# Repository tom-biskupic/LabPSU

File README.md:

# LabPSU
Open Source Lab Power Supply

This project is to create an open source modular lab power supply. The power supply is designed to:

* Provide between 0-15V @ 5A and 15-30V @ 3A
* Provide current limiting
* Voltage to be settable to within 1mV and current limit to 1mA resolution.
* Voltage/current readback to 1mV and 1mA with low temperature drift.
* Limit heat loss through the use of a pre-regulator. The pre-regulator uses an SCR and MOSFET arrangement to reduce noise (switches at a low frequency)
* Digitally controllable via a Raspberry PI and touch-screen interface.
* Multiple channels (designed for 3).
* Each channel is isolated and can be paralleled or put in series.
* Each channel uses its own torroidal transformer.

A Blog documenting the development of the project can be found here http://wahz.blogspot.com.au/2015/03/lab-power-supply-project.html

The major components used in the project are:

* IRFP044N N-channel MOSFET as the pass device. http://www.irf.com/product-info/datasheets/data/irfp044n.pdf
* IRF5210 P-channel MOSFET used to switch the input in the pre-regulator http://www.irf.com/product-info/datasheets/data/irf5210.pdf
* MCR-100 SCR http://www.onsemi.com/pub_link/Collateral/MCR100-D.PDF
* LT1639 Op Amps used in the control loop. http://www.linear.com/product/LT1639
* LT1716 Comparator used in the pre-regulator http://cds.linear.com/docs/en/datasheet/1716fa.pdf
* LTC2050 Op Amp used for current sense amplifier. http://www.linear.com/product/LTC2050
* AD5689R DAC with built in 2ppm/degree reference as main output voltage/current DAC. http://www.analog.com/media/en/technical-documentation/data-sheets/AD5689_5687.pdf
* AD7705 ADC used to read output voltage/current http://www.analog.com/media/en/technical-documentation/data-sheets/AD7705_7706.pdf
* ATMEGA328P Used as the main controller
* ADUM1201 dual channel isolator used to isolate the USB interface from the rest of the module http://www.analog.com/media/en/technical-documentation/data-sheets/ADuM1200_1201.pdf
* MCP2200 USB to serial converter http://www.microchip.com/wwwproducts/devices.aspx?dDocName=en546923

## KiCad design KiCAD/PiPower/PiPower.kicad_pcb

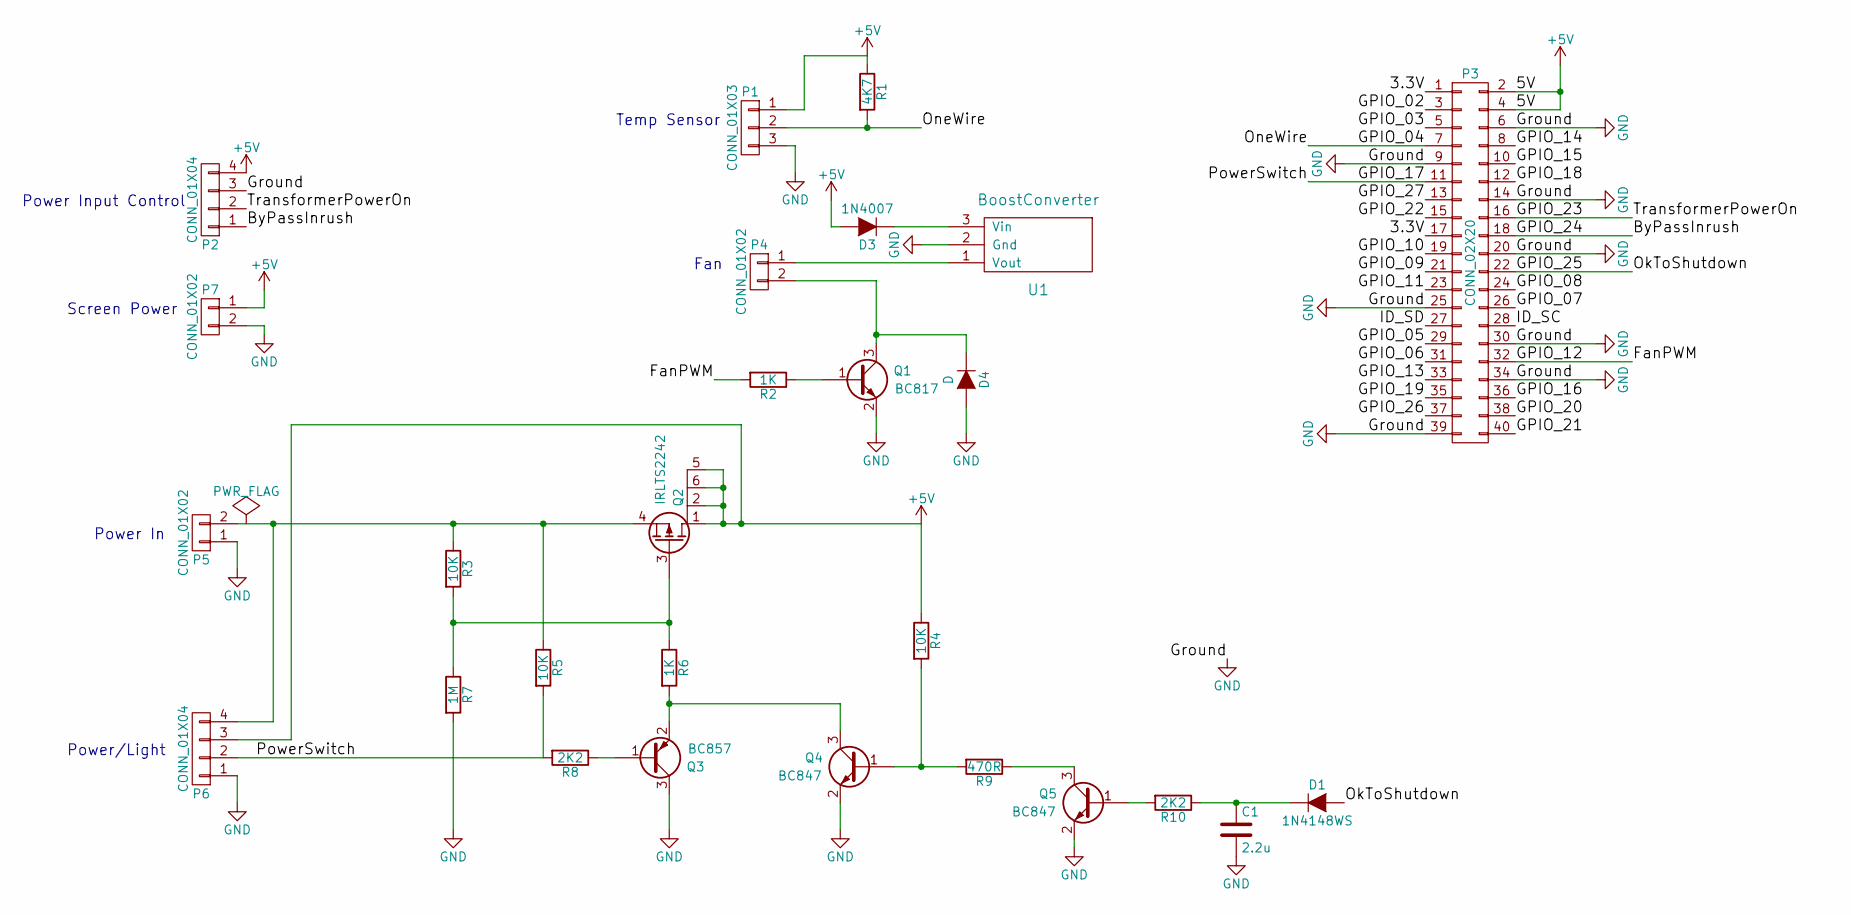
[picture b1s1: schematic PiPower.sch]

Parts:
C1: 2.2u; C_0805
D1: 1N4148WS; SOD-323
D3: 1N4007; Diode_DO-41_SOD81_Horizontal_RM10
D4: D; SOD-323
P1: CONN_01X03; ThreePinSmall
P2, P6: CONN_01X04; PINHeader1-4
P3: CONN_02X20; Pin_Header_Straight_2x20
P4: CONN_01X02; TwoPinSmall
P5: CONN_01X02; WCON-2PIN
P7: CONN_01X02; Pin_Header_Straight_1x02
Q1: BC817; SOT-23
Q2: IRLTS2242
Q3: BC857; SOT-23
Q4, Q5: BC847; SOT-23
R1: 4K7; R_0805
R2, R6: 1K; R_0805
R3, R4, R5: 10K; R_0805
R7: 1M; R_0805
R8, R10: 2K2; R_0805
R9: 470R; R_0805
U1: BoostConverter

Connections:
+5V: D3.2 (A), P1.1, P2.4, P3.2, P3.4, P6.3, P7.1, Q2.1 (D), Q2.2 (D), Q2.5 (D), Q2.6 (D), R1.1, R4.1
/3.3V: P3.1, P3.17
/ByPassInrush: P2.1, P3.18
/FanPWM: P3.32, R2.2
/GPIO_02: P3.3
/GPIO_03: P3.5
/GPIO_04: P1.2, P3.7, R1.2
/GPIO_05: P3.29
/GPIO_06: P3.31
/GPIO_07: P3.26
/GPIO_08: P3.24
/GPIO_09: P3.21
/GPIO_10: P3.19
/GPIO_11: P3.23
/GPIO_13: P3.33
/GPIO_14: P3.8
/GPIO_15: P3.10
/GPIO_16: P3.36
/GPIO_17: P3.11, P6.2, R5.2, R8.2
/GPIO_18: P3.12
/GPIO_19: P3.35
/GPIO_20: P3.38
/GPIO_21: P3.40
/GPIO_22: P3.15
/GPIO_23: P2.2, P3.16
/GPIO_25: D1.2 (A), P3.22
/GPIO_26: P3.37
/GPIO_27: P3.13
/ID_SC: P3.28
/ID_SD: P3.27
GND: C1.2, D4.2 (A), P1.3, P2.3, P3.6, P3.9, P3.14, P3.20, P3.25, P3.30, P3.34, P3.39, P5.1, P6.1, P7.2, Q1.2 (E), Q3.3 (C), Q4.2 (E), Q5.2 (E), R7.2, U1.2 (Gnd)
unnamed: C1.1, D1.1 (K), R10.1
unnamed: D3.1 (K), U1.3 (Vin)
unnamed: D4.1 (K), P4.2, Q1.3 (C)
unnamed: P4.1, U1.1 (Vout)
unnamed: P5.2, P6.4, Q2.4 (S), R3.1, R5.1
unnamed: Q1.1 (B), R2.1
unnamed: Q2.3 (G), R3.2, R6.1, R7.1
unnamed: Q3.1 (B), R8.1
unnamed: Q3.2 (E), Q4.3 (C), R6.2
unnamed: Q4.1 (B), R4.2, R9.2
unnamed: Q5.1 (B), R10.2
unnamed: Q5.3 (C), R9.1

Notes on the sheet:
Power/Light
Power In
Power Input Control
Temp Sensor
Fan
Screen Power

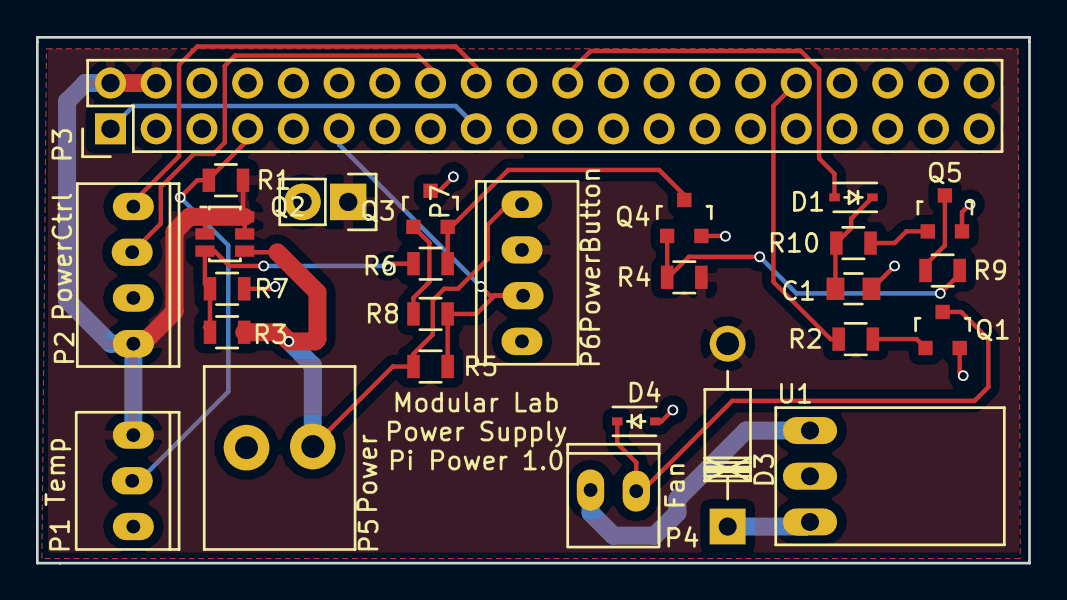
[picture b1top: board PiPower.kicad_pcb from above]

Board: 2 copper layers, 55.1 x 29.2 mm, 27 parts (0 on the bottom side), 21 nets.

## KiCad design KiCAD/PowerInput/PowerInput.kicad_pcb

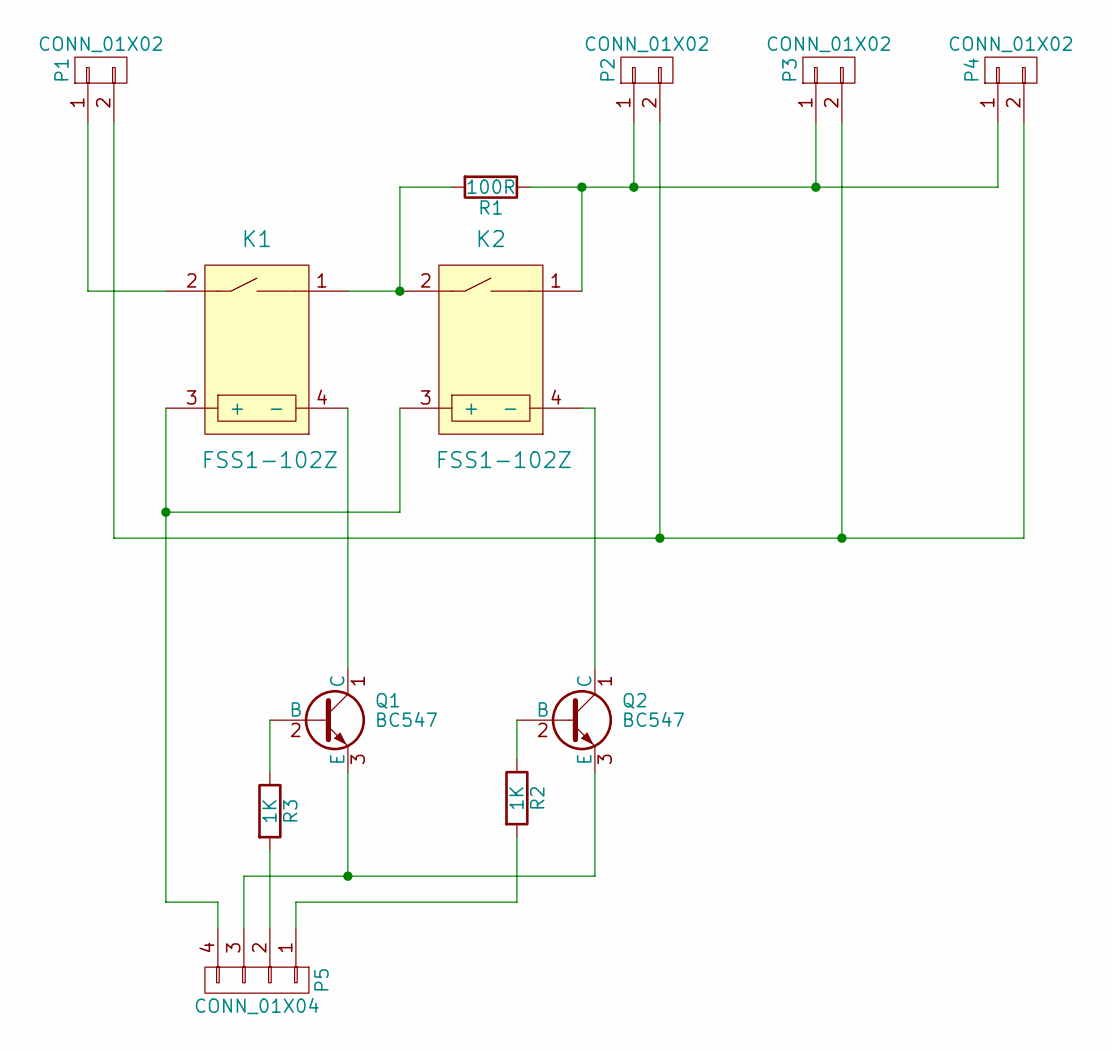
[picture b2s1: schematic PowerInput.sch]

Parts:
K1, K2: FSS1-102Z
P1, P2, P3, P4: CONN_01X02; WCON-2PIN
P5: CONN_01X04; PINHeader1-4
Q1, Q2: BC547; TO-92_Inline_Narrow_Oval
R1: 100R; Resistor_Ceramic_Horizontal_L50mm-W14mm-H13mm-p60mm
R2, R3: 1K; Resistor_Horizontal_RM10mm

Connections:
unnamed: K1.1, K2.2, R1.2
unnamed: K1.2, P1.1
unnamed: K1.3 (+), K2.3 (+), P5.4
unnamed: K1.4 (-), Q1.1 (C)
unnamed: K2.1, P2.1, P3.1, P4.1, R1.1
unnamed: K2.4 (-), Q2.1 (C)
unnamed: P1.2, P2.2, P3.2, P4.2
unnamed: P5.1, R2.2
unnamed: P5.2, R3.2
unnamed: P5.3, Q1.3 (E), Q2.3 (E)
unnamed: Q1.2 (B), R3.1
unnamed: Q2.2 (B), R2.1

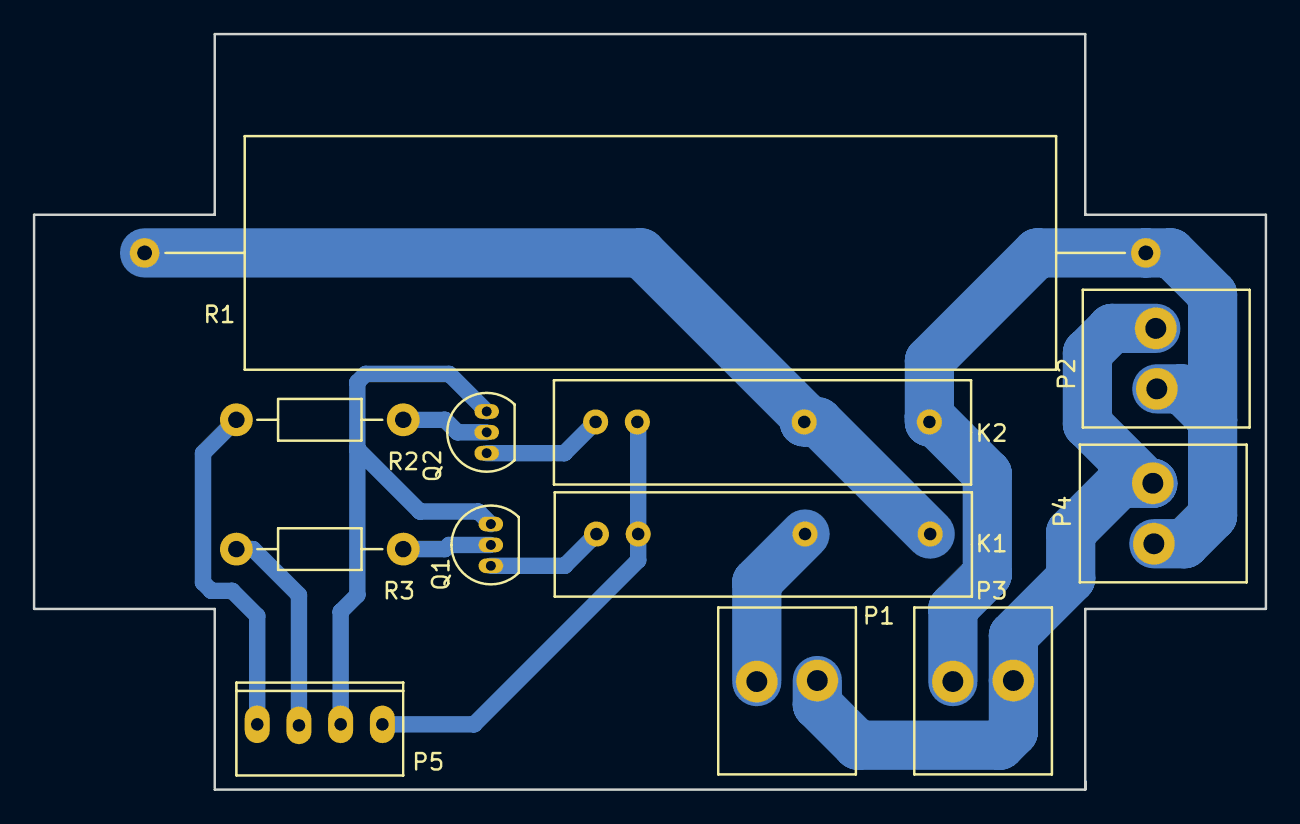
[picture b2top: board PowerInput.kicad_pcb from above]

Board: 2 copper layers, 75.0 x 46.0 mm, 12 parts (0 on the bottom side), 12 nets.

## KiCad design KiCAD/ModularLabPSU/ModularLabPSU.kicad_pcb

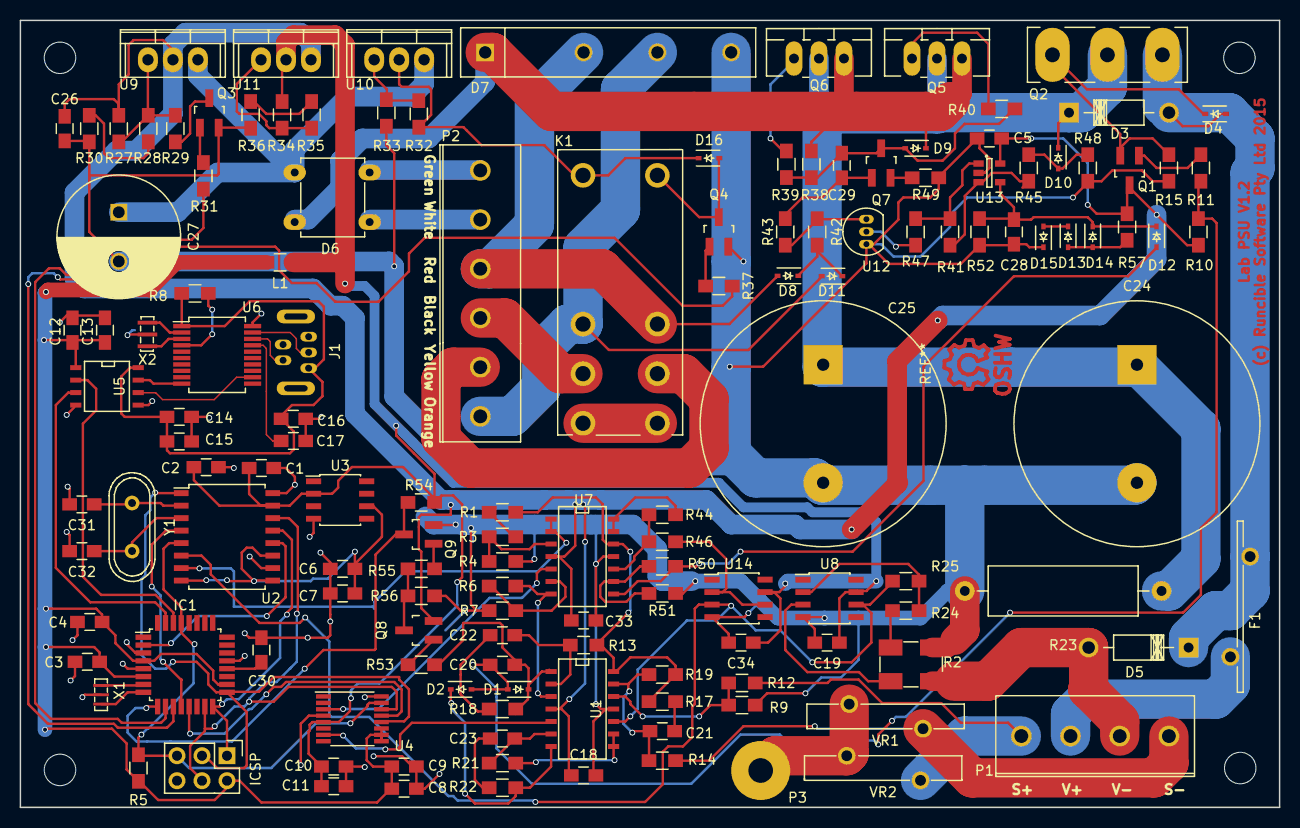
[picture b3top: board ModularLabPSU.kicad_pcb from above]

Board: 2 copper layers, 128.0 x 80.0 mm, 141 parts (0 on the bottom side), 105 nets.

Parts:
C1, C8, C11, C28: 10uF; C_0805_HandSoldering
C2, C3, C4, C5, C6, C9, C10, C13, C15, C16, C17, C18, C19, C26, C30, C33, C34: 0.1uF; C_0805_HandSoldering
C7: 1uF; C_0805_HandSoldering
C12, C14: 10nF; C_0805_HandSoldering
C20, C29: 1nF; C_0805_HandSoldering
C21: 4.7pF; C_0805_HandSoldering
C22: 100pF; C_0805_HandSoldering
C23: 100p; C_0805_HandSoldering
C24, C25: 4700uF; RS_C4700uF_63V
C27: 200uF; C_Radial_D12.5_L25_P5
C31, C32: 20pF; C_0805_HandSoldering
D1, D2, D16: 1N4148WS; SOD-323
D3, D5: 1N4007; Diode_DO-41_SOD81_Horizontal_RM10
D4: 18V; SOD-323
D6: DF06M; DiodesIncDF06M
D7: Diode_BridgeGBJ106; DIODE_BRIDGE_GBJ1506
D8, D11, D12, D13, D14, D15: D; SOD-323
D9: DDZ18CSF-7; SOD-323
D10: 3V3; SOD-323
F1: 5A PTC; BOURNSMF-R500
IC1: ATMEGA328P-A; TQFP-32_7x7mm_Pitch0.8mm
ICSP: AVR-ISP-6; Pin_Header_Straight_2x03
J1: USB_MINI_B_OTG; MOLEX-USB-OTG-MINI-STRAIGHT
K1: HF115F
L1: 220 Ohm Ferrite; R_0805_HandSoldering
P1: CONN_01X04; RS5mmClampTerminal
P2: CONN_01X06; 6PosRS5mmClampTerminal
P3: EarthWire; SolderWirePad_single_2-5mmDrill
Q1, Q3, Q4, Q7, Q9: BC847B; SOT-23_Handsoldering
Q2: IRFP044N; TO-247_Vertical_Neutral123_largePads
Q5, Q6: IRFP5210; TO-220_Neutral123_Vertical_LargePads
Q8: BC857; SOT-23_Handsoldering
R1, R39, R40, R49: 100R; R_0805_HandSoldering
R2: 10m; VCS1625
R3, R6, R21, R29, R43, R44, R46, R50, R51, R52, R53: 10K; R_0805_HandSoldering
R4, R7: 2K; R_0805_HandSoldering
R5, R15, R48: 4K7; R_0805_HandSoldering
R8, R54: 4.7K; R_0805_HandSoldering
R9, R12, R14, R19: 100K*; R_0805_HandSoldering
R10: 47K; R_0805_HandSoldering
R11: 2K2; R_0805_HandSoldering
R13, R55, R56, R57: 22K; R_0805_HandSoldering
R17, R22: 5K1; R_0805_HandSoldering
R18: 5.1K; R_0805_HandSoldering
R23: 4K7; Resistor_Horizontal_RM20mm
R24: 10R; R_0805_HandSoldering
R25, R30, R38: 1K; R_0805_HandSoldering
R27, R34: 240R; R_0805_HandSoldering
R28: 6K2; R_0805_HandSoldering
R31: 2.2K; R_0805_HandSoldering
R32: 240; R_0805_HandSoldering
R33: 4K3; R_0805_HandSoldering
R35: 680R; R_0805_HandSoldering
R36: 47R; R_0805_HandSoldering
R37: 1k; R_0805_HandSoldering
R41: 470K; R_0805_HandSoldering
R42: 3K3; R_0805_HandSoldering
R45: 220R; R_0805_HandSoldering
R47: 330K; R_0805_HandSoldering
U1, U7: LT1639; SOIC-14_N
U2: AD7705BRUZ; SOIC-16_7.5x10.3mm_Pitch1.27mm
U3: AD780BRZ; SOIC-8_3.9x4.9mm_Pitch1.27mm
U4: AD5689; TSSOP-16_4.4x5mm_Pitch0.65mm
U5: ADUM1201ARZ-RL7; SOIC-8-N
U6: MCP2200; SSOP-20_5.3x7.2mm_Pitch0.65mm
U8, U14: LTC2050; SOIC-8_3.9x4.9mm_Pitch1.27mm
U9: LM317HVT; TO-220
U10, U11: LM317AT; TO-220
U12: SCR; TO-92_Inline_Narrow_Oval
U13: LT1716; SOT-23-5
VR1, VR2: VR; V275LA20AP
X1: 20MHz; CSTCE_V
X2: 12MHz; CSTCE_G
Y1: 2MHz; Crystal_HC49-U_Vertical

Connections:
+5V: C1.1, C2.1, C10.1, C11.1, C19.1, C34.1, L1.1, R34.1, R54.1, U2.15, U3.2, U4.5, U8.7, U11.2, U14.7
+5VD: C3.1, C4.1, C8.1, C9.1, C12.1, C13.1, IC1.4, IC1.6, IC1.18, ICSP.2, L1.2, R5.1, U4.9, U4.10, U4.11, U5.1
+24V: D16.1, K1.8, R32.1, U10.2
/DigitalControl/ADC-CS: IC1.12, U2.4
/DigitalControl/DAC-CS: IC1.13, U4.13
/DigitalControl/MISO: IC1.16, ICSP.1, U2.13
/DigitalControl/MOSI: IC1.15, ICSP.4, U2.14, U4.14
/DigitalControl/Reset: IC1.29, ICSP.5, R5.2, U2.5, U4.15
/DigitalControl/SCK: IC1.17, ICSP.3, U2.1, U4.12
AC1: D7.2, D8.2, K1.2, P2.3
AC2: D7.3, D11.2, K1.7, P2.6
CCMode: IC1.9, Q9.3, R54.2
Earth_Protective: P3.1, VR1.2, VR2.2
ISet: U1.5, U4.7
Ioutmon: R25.1, U1.10, U2.6, U8.6, U14.3
unnamed: C6.1, C7.1, U2.8, U2.9, U2.11, U3.6
unnamed: C17.1, U6.17
unnamed: C20.1, D1.1, R18.2, R53.2, U1.1
unnamed: C20.2, D1.2, D2.2, R10.2, R11.1
unnamed: C21.1, R14.2, R19.1, U1.13
unnamed: C21.2, R17.1
unnamed: C22.1, R13.2, U1.2
unnamed: C22.2, R18.1
unnamed: C23.1, R21.2, U1.6
unnamed: C23.2, R22.1
unnamed: C27.1, D6.3, U9.3, U10.3
unnamed: C28.1, D12.1, D14.1, R52.1, U13.4
unnamed: C29.1, D9.2, Q7.3, R38.2, R39.2, R40.2
unnamed: C29.2, Q7.1, R43.1
unnamed: C30.1, IC1.20
unnamed: C31.1, U2.2, Y1.1
unnamed: C32.1, U2.3, Y1.2
unnamed: D2.1, R22.2, U1.7
unnamed: D3.2, D4.2, D5.1, F1.1, Q2.3
unnamed: D4.1, Q1.2, Q2.1, R15.1
unnamed: D5.2, P1.3, R2.I2
unnamed: D6.1, P2.2
unnamed: D6.2, P2.1
unnamed: D10.2, R45.1, R48.1
unnamed: D8.1, D11.1, R42.1
unnamed: D12.2, R50.1, U7.8
unnamed: D13.1, D15.2
unnamed: D13.2, D14.2, R57.2
unnamed: D16.2, K1.1, Q4.3
unnamed: F1.2, P1.2
unnamed: IC1.2, U2.12
unnamed: IC1.7, X1.3
unnamed: IC1.8, X1.1
unnamed: IC1.30, U5.2
unnamed: IC1.31, U5.3
unnamed: J1.2, U6.18
unnamed: J1.3, U6.19
unnamed: K1.3, P2.5
unnamed: K1.4, K1.5
unnamed: K1.6, P2.4
unnamed: P1.1, R12.1, VR2.1
unnamed: P1.4, R14.1, VR1.1
unnamed: Q1.1, R11.2
unnamed: Q3.1, R31.2
unnamed: Q3.3, R29.2
unnamed: Q4.1, R37.2
unnamed: Q5.1, R40.1
unnamed: Q6.1, R39.1
unnamed: Q7.2, R49.1
unnamed: Q8.1, R53.1
unnamed: Q8.3, R55.2, R56.1
unnamed: Q9.1, R55.1
unnamed: R1.2, R3.1
unnamed: R2.E1, R24.2
unnamed: R2.E2, U8.3
unnamed: R3.2, R4.1, U7.3
unnamed: R6.2, R7.1, U7.6
unnamed: R8.2, U6.4
unnamed: R9.2, R12.2, U1.12
unnamed: R21.1, U1.8, U1.9
unnamed: R24.1, R25.2, U8.2
unnamed: R27.2, R28.1, R29.1, U9.1
unnamed: R28.2, R30.1
unnamed: R32.2, R33.1, U10.1
unnamed: R34.2, R35.1, U11.1
unnamed: R35.2, R36.1
unnamed: R41.1, R47.2, U13.1
unnamed: R41.2, R45.2, U13.3
unnamed: R42.2, R43.2, U12.3
unnamed: R44.1, R46.1, U7.10
unnamed: R44.2, U7.13, U7.14
unnamed: R46.2, U14.2, U14.6
unnamed: R47.1, U12.2
unnamed: R50.2, R51.1, U7.9
unnamed: U2.7, U7.1, U7.2
unnamed: U4.3, U7.5
unnamed: U5.6, U6.12
unnamed: U5.7, U6.10
unnamed: U6.2, X2.1
unnamed: U6.3, X2.3
SetVPlus: IC1.10, R31.1
USBGND: C14.2, C15.2, C16.2, C17.2, J1.5, U5.5, U6.20, X2.2
VCC: C5.1, C18.1, C26.1, C33.1, Q1.3, Q8.2, R10.1, R27.1, R57.1, U1.4, U7.4, U9.2, U11.3, U13.5
VRelay: IC1.11, R37.1
VSet: R6.1, U1.3, U7.7
VUSB: C14.1, C15.1, C16.1, J1.1, R8.1, U5.8, U6.1
Voutmon: R1.1, R13.1, R17.2, R19.2, U1.14, U7.12
Vprereg: C24.1, C25.1, D3.1, D10.1, Q2.2, Q5.2, Q6.2, R23.1
Vrect+: D6.4, D7.1, D9.1, Q5.3, Q6.3, R38.1
Vrect-: C1.2, C2.2, C3.2, C4.2, C5.2, C6.2, C7.2, C8.2, C9.2, C10.2, C11.2, C12.2, C13.2, C18.2, C19.2, C24.2, C25.2, C26.2, C27.2, C28.2, C30.2, C31.2, C32.2, C33.2, C34.2, D7.4, D15.1, IC1.3, IC1.5, IC1.21, ICSP.6, Q3.2, Q4.2, Q9.2, R2.I1, R4.2, R7.2, R9.1, R15.2, R23.2, R30.2, R33.2, R36.2, R48.2, R49.2, R51.2, R52.2, R56.2, U1.11, U2.10, U2.16, U3.4, U4.4, U4.16, U5.4, U7.11, U8.4, U12.1, U13.2, U14.4, X1.2

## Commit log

2015-12-15 Initial commit of KiCAD files and readme
2015-12-15 Hmm not picking up changes
2015-12-15 Added firmware files
2015-12-15 Added Python/Kivy control skeleton. Still WIP
2015-12-15 Oops accidentally added idea directory
2015-12-16 Implemented output enable and command to check if we are in current limit mode
2015-12-16 Dammit missed the project files
2015-12-16 Missed adding the Command for testing if we are in CC mode. Fixed the command name. Fixed a crash when invalid command is entered
2015-12-16 Wrong port thing for CC mode. Also made it so always not in CC mode when disabled
2015-12-30 Split into files. Experimented with a yellow border (still needs work). Added Code to interface with the actual power supply and added unit test for power supply interface code
2016-03-10 Re-enabled the ADC, got rid of some printfs and added a command to set the output from a count value (for calibration)
2016-03-16 ADC Cal table updated. Added command to get ADC count (for calibration)
2016-03-16 Untabified code
2016-03-29 Syncing changes
2016-04-03 Moved to pySerial, work on integrating with actual PSU.
2016-04-05 More GUI work and bug fixes
2016-04-06 Added Calibration code based on PowerSupplyChannel
2016-04-19 Started re-design of PCB. Schematic changes from testing first board and started developing new layout
2016-04-29 Missing files
2016-05-19 Cal changes
2016-05-20 Added Linearizer for current ADC/DAC. Added some cal data to see how good the current reading is
2016-05-21 More work on calibration code
2016-05-21 Starting to add some controls to close and configure
2016-05-21 Missed a file
2016-06-20 Added second channel
2016-07-07 Added KiCAD project for power input control and added (start of) PI soft-switch project
2016-08-10 Completed PiPower board design
2016-08-22 Some GUI changes to re-orient horizontally
2016-08-22 Raspberry Pi Power control board
2016-08-22 Missed a couple of stars on precision resistors
2016-08-31 Added temperature sensing and temperate display. Added fan control based on temperature. All three channels added
2016-09-01 Changed PowerSupplyChannel to be async (i.e. thread). Still testing. TBD
2016-09-02 More work on running the channel interface in a thread
2016-09-02 Minor GUI changes
2016-09-02 Fixed switch callback
2016-09-03 Work on Calibrate GUI
2016-09-06 More work on Calibrator GUI
2016-09-12 Implemented storage/retrieval of cal constants from EEPROM and commands to get/set those constants. Untested
2016-09-14 Moved LabPSU pointer out of command to save memory. Reduced default cal data to three points to save memory. Reduced cal table to 16 points to save memory
2016-09-14 Added more meat to calibrate code
2016-09-14 Changed the way the dialogs communicate so cancelation is handlded better. Fixed a few bugs
2016-09-15 Added code to make calibration commands respond
2016-10-01 Changed the timing a bit to make the PSU more responsive. Also changed the GUI to pause all channel updates (not just the channel you clicked) when a dialog is opened.
2017-04-25 Added code to save the previous settings and reload them at startup
2017-04-25 Fixed settings saving code so it will use home directory
2017-05-17 Fixed a case-sensitivity issue that stopped the schematic opening on Linux
2017-09-06 Added PDFs of Schematics
2017-09-06 Removed wrong filename files
2017-09-06 Now realized channel PDFs include sub-sheets so moved these into just one PDF
2018-06-16 Changes to add more resoluition at low voltages/currents
2019-07-07 Python3 changes
2022-01-08 Dev - backup
2022-02-15 Added SCPI Control
